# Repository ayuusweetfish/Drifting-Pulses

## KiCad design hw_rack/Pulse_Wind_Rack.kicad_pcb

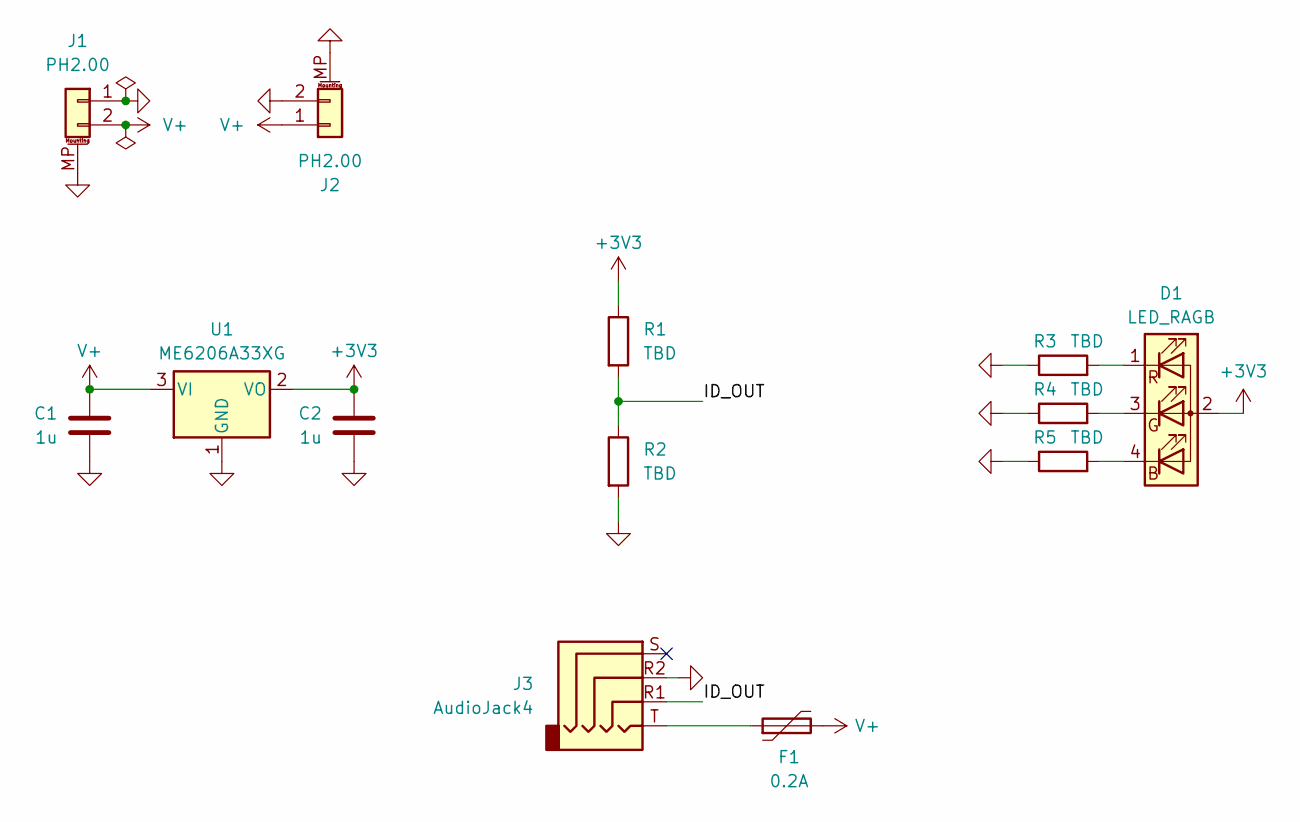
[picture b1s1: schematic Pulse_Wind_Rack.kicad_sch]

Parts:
C1, C2: 1u; C_0402_1005Metric
D1: LED_RAGB; LED_D5.0mm-4_RGB
F1: 0.2A; Fuse_0603_1608Metric
J1, J2: PH2.00; JST_PH_S2B-PH-SM4-TB_1x02-1MP_P2.00mm_Horizontal
J3: AudioJack4; Jack_3.5mm_KoreanHropartsElec_PJ-320D-4A_Horizontal
R1, R2, R3, R4, R5: TBD; R_0402_1005Metric
U1: ME6206A33XG; SOT-23

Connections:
+3V3: C2.2, D1.2 (A), R1.1, U1.2 (VO)
/ID_OUT: J3.R1, R1.2, R2.1
GND: C1.1, C2.1, J1.1, J1.MP (MountPin), J2.2, J2.MP (MountPin), J3.R2, R2.2, R3.1, R4.1, R5.1, U1.1 (GND)
unnamed: D1.4 (BK), R5.2
unnamed: D1.3 (GK), R4.2
unnamed: D1.1 (RK), R3.2
unnamed: F1.1, J3.T
V+: C1.2, F1.2, J1.2, J2.1, U1.3 (VI)

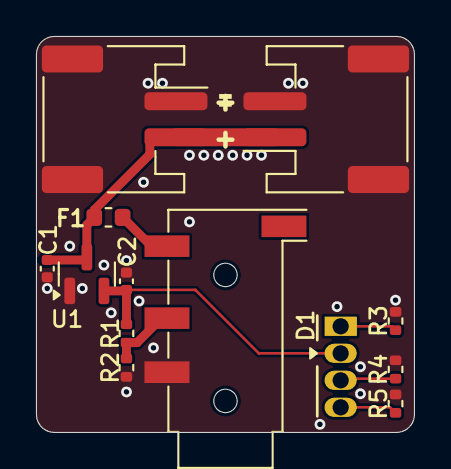
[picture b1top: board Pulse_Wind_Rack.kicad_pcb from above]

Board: 2 copper layers, 21.0 x 22.0 mm, 13 parts (0 on the bottom side), 8 nets.

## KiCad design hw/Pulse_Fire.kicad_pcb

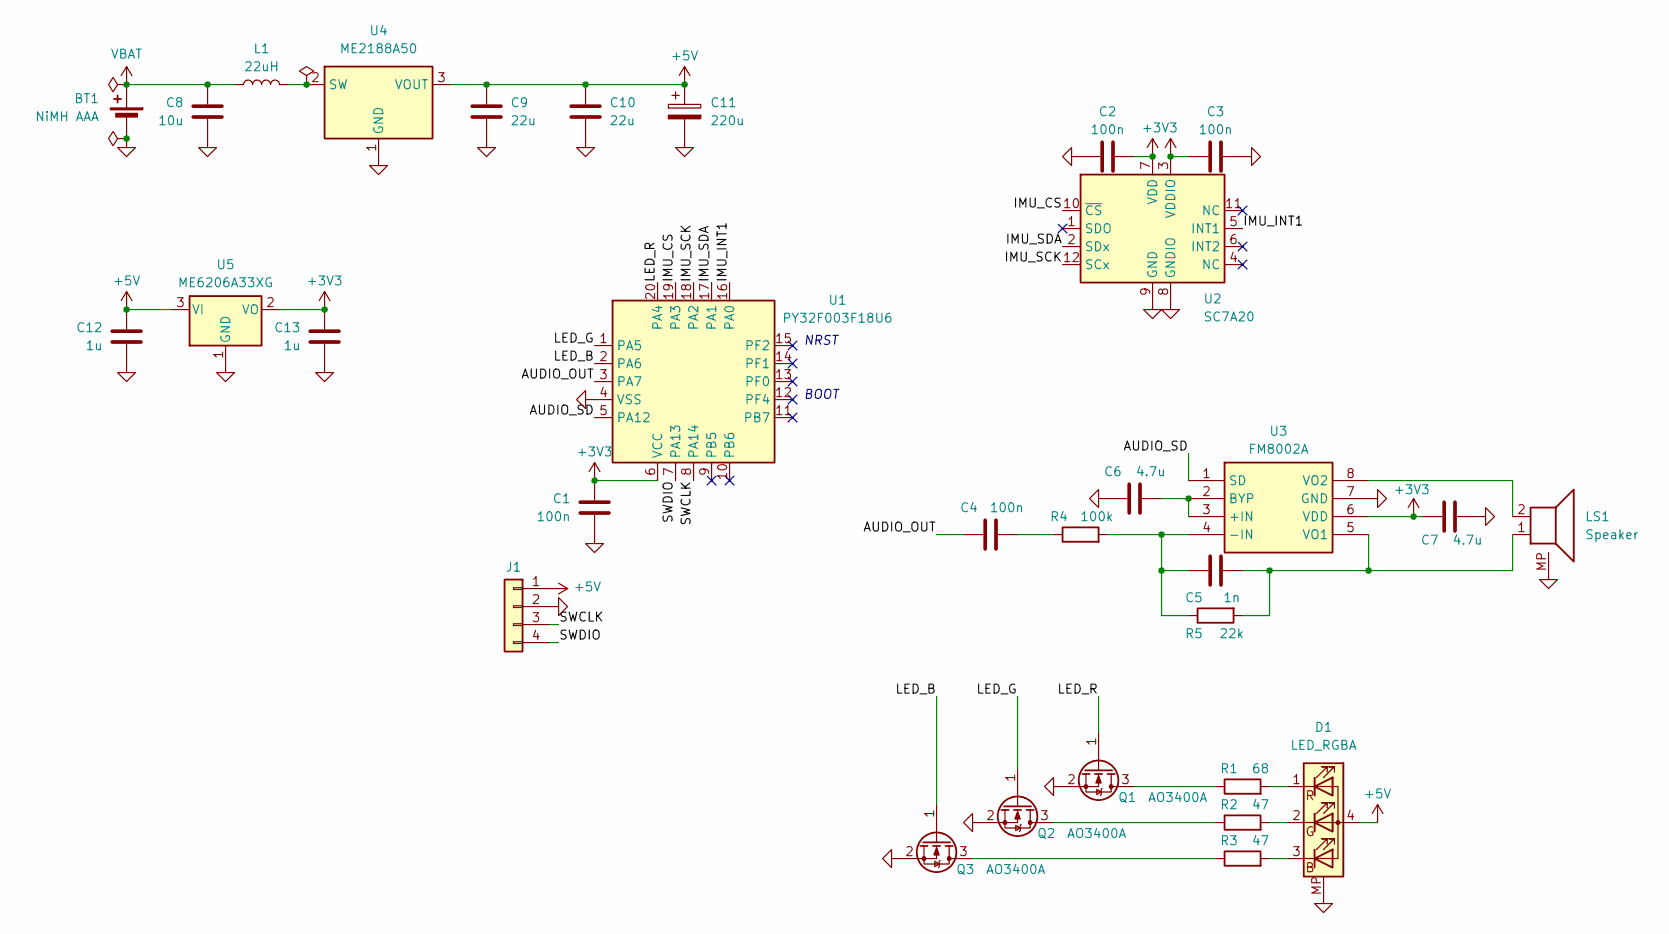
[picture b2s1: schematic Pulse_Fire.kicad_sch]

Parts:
BT1: NiMH AAA; BatteryHolder_Keystone_2466_1xAAA
C1, C2, C3, C4: 100n; C_0402_1005Metric
C5: 1n; C_0402_1005Metric
C6, C7: 4.7u; C_0402_1005Metric
C8: 10u; C_0402_1005Metric
C9, C10: 22u; C_0603_1608Metric
C11: 220u; CP_Elec_6.3x5.4
C12, C13: 1u; C_0402_1005Metric
D1: LED_RGBA; JST_PH_S4B-PH-SM4-TB_1x04-1MP_P2.00mm_Horizontal
J1: Conn_01x04; TestPoints_1x04_P2.00
L1: 22uH; L_Sunlord_SWPA4030S
LS1: Speaker; JST_PH_S2B-PH-SM4-TB_1x02-1MP_P2.00mm_Horizontal
Q1, Q2, Q3: AO3400A; SOT-23
R1: 68; R_0603_1608Metric
R2, R3: 47; R_0603_1608Metric
R4: 100k; R_0402_1005Metric
R5: 22k; R_0402_1005Metric
U1: PY32F003F18U6; QFN-20-1EP_3x3mm_P0.4mm_EP1.65x1.65mm
U2: SC7A20; LGA-12_2x2mm_P0.5mm
U3: FM8002A; SOP-8_3.9x4.9mm_P1.27mm; Manufacturer_Part_Number MD8002A
U4: ME2188A50; SOT-23
U5: ME6206A33XG; SOT-23

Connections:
+3V3: C1.2, C2.2, C3.1, C7.1, C13.2, U1.6 (VCC), U2.3 (VDDIO), U2.7 (VDD), U3.6 (VDD), U5.2 (VO)
+5V: C9.2, C10.2, C11.1, C12.2, D1.4 (A), J1.1, U4.3 (VOUT), U5.3 (VI)
/AUDIO_OUT: C4.1, U1.3 (PA7)
/AUDIO_SD: U1.5 (PA12), U3.1 (SD)
/IMU_CS: U1.19 (PA3), U2.10 (~CS)
/IMU_INT1: U1.16 (PA0), U2.5 (INT1)
/IMU_SCK: U1.18 (PA2), U2.12 (SCx)
/IMU_SDA: U1.17 (PA1), U2.2 (SDx)
/LED_B: Q3.1 (G), U1.2 (PA6)
/LED_G: Q2.1 (G), U1.1 (PA5)
/LED_R: Q1.1 (G), U1.20 (PA4)
/SWCLK: J1.3, U1.8 (PA14)
/SWDIO: J1.4, U1.7 (PA13)
GND: BT1.2 (-), C1.1, C2.1, C3.2, C6.1, C7.2, C8.1, C9.1, C10.1, C11.2, C12.1, C13.1, D1.MP, J1.2, LS1.MP, Q1.2 (S), Q2.2 (S), Q3.2 (S), U1.4 (VSS), U1.21 (PAD), U2.8 (GNDIO), U2.9 (GND), U3.7 (GND), U4.1 (GND), U5.1 (GND)
unnamed: C4.2, R4.1
unnamed: D1.3 (BK), R3.2
unnamed: D1.2 (GK), R2.2
unnamed: D1.1 (RK), R1.2
unnamed: Q1.3 (D), R1.1
unnamed: Q2.3 (D), R2.1
unnamed: Q3.3 (D), R3.1
unnamed: C6.2, U3.2 (BYP), U3.3 (+IN)
unnamed: C5.1, R4.2, R5.1, U3.4 (-IN)
unnamed: C5.2, LS1.1, R5.2, U3.5 (VO1)
unnamed: LS1.2, U3.8 (VO2)
unnamed: L1.2, U4.2 (SW)
VBAT: BT1.1 (+), C8.2, L1.1

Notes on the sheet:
NRST
BOOT

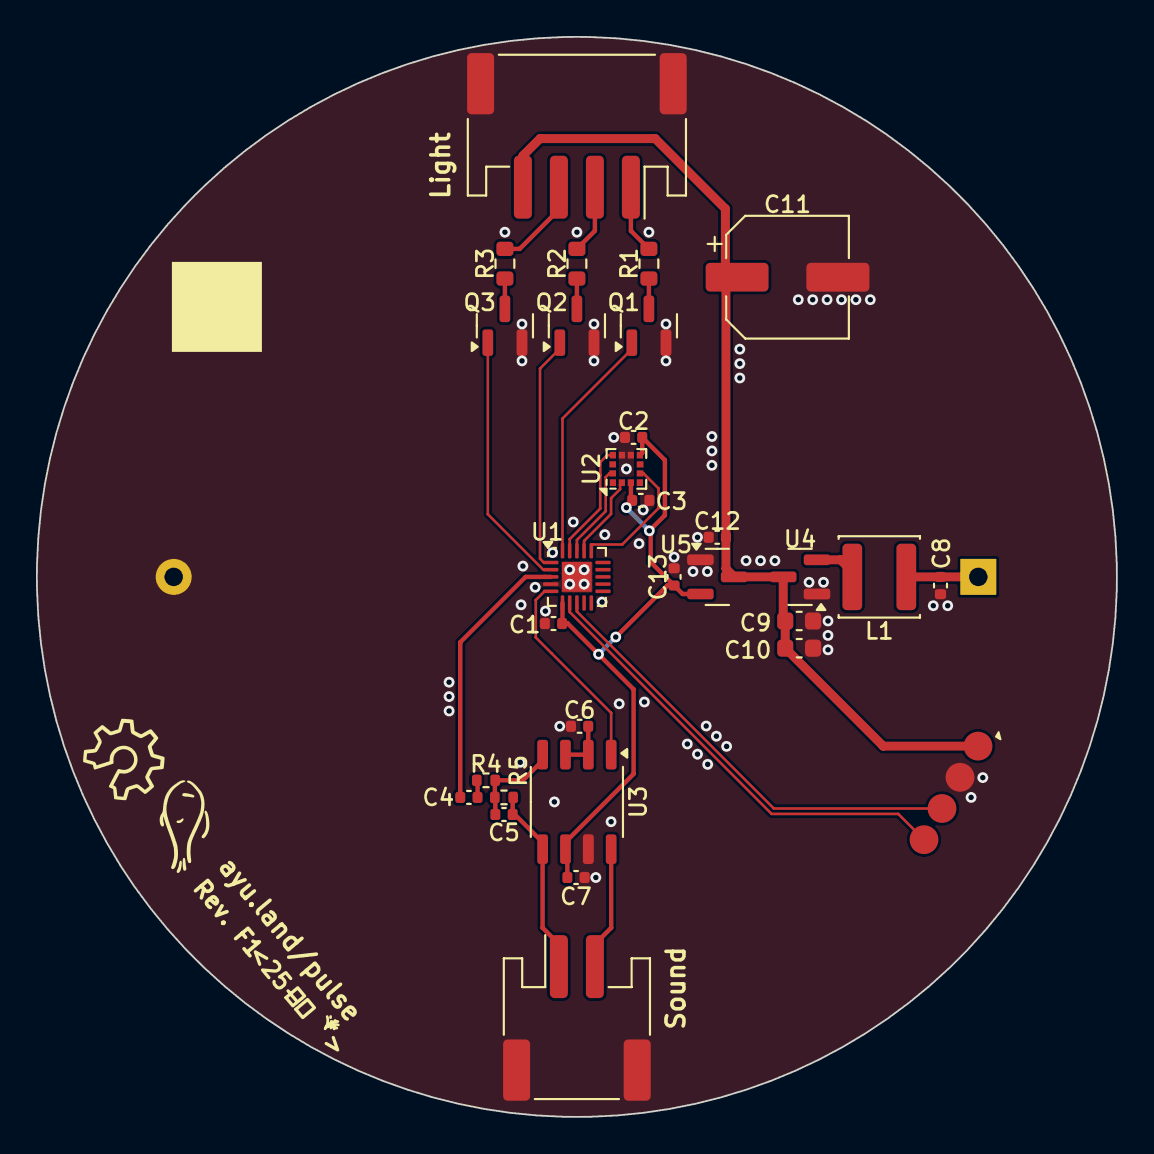
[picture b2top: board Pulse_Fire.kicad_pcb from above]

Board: 2 copper layers, 60.0 x 60.0 mm, 31 parts (1 on the bottom side), 27 nets.

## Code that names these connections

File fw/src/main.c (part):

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  HAL_GPIO_Init(GPIOA, &(GPIO_InitTypeDef){
    .Mode = GPIO_MODE_AF_PP,
    .Pin = (1 << 4) | (1 << 5),
    .Alternate = 13,  // PA4 = TIM3_CH3, PA5 = TIM3_CH2
    .Speed = GPIO_SPEED_FREQ_HIGH,
  });
  HAL_GPIO_Init(GPIOA, &(GPIO_InitTypeDef){
    .Mode = GPIO_MODE_AF_PP,
    .Pin = (1 << 6),
    .Alternate = 1,   // PA6 = TIM3_CH1
    .Speed = GPIO_SPEED_FREQ_HIGH,
  });

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
  // ============ Audio output ============ //
{
  // PA12 = AUDIO_SD
  GPIOA->BSRR = (1 << 12);  // High = disable
  HAL_GPIO_Init(GPIOA, &(GPIO_InitTypeDef){
    .Mode = GPIO_MODE_OUTPUT_PP,
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  HAL_GPIO_Init(GPIOA, &(GPIO_InitTypeDef){
    .Mode = GPIO_MODE_AF_PP,
    .Pin = (1 << 7),
    .Alternate = 5,   // PA7 = TIM17_CH1
    .Speed = GPIO_SPEED_FREQ_HIGH,
  });
  HAL_TIM_PWM_Init(&tim17);
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    },
  };
  HAL_SPI_Init(&spi1);
  GPIOA->BSRR = (1 << 3);   // IMU_CS high
  HAL_GPIO_Init(GPIOA, &(GPIO_InitTypeDef){
    .Mode = GPIO_MODE_OUTPUT_PP,
    .Pin = (1 << 3),
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  HAL_GPIO_Init(GPIOA, &(GPIO_InitTypeDef){
    .Mode = GPIO_MODE_AF_PP,
    .Pin = (1 << 1) | (1 << 2),
    .Alternate = 10,  // PA1 = SPI1_MOSI, PA2 = SPI1_SCK
  });
}

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  printf("IMU FIFO cleared\n");

if (0)
  GPIOA->BSRR = (1 << 12) << 16;  // Enable by AUDIO_SD

  while (1) {
    bool pat = false;
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
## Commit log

2025-08-05 hw: Bob-part schematic
2025-08-05 hw: Layout & routing
2025-08-05 hw: Tweaks in the details
2025-08-05 hw: Adjust silkscreen
2025-08-05 hw: Finalize board design
2025-08-06 hw: Fix errors (> <)
2025-08-06 hw: Connect SC7A20 NC (pin 4) to GND?
2025-08-06 hw: Minor tweaks; finalize
2025-08-06 hw: Rack schematic
2025-08-06 fw: Rack board? To be revised
2025-08-06 fw: Revise rack board layout & routing
2025-08-06 hw: Finalize rack board design
2025-08-07 hw: Schematic
2025-08-07 hw: Revise schematic to use discrete MOSFETs
2025-08-08 hw: Schematic -- add mounting pins for JST connectors
2025-08-08 hw: Complete board design
2025-08-08 hw: Detail nudges
2025-08-08 hw: Place silkscreen
2025-08-08 hw: Embed fonts; revise silkscreen
2025-08-08 hw: Output Gerbers
2025-08-09 mech: Add rack 3D model
2025-08-09 mech: Save block material
2025-08-09 mech: Split shell's front side into separate part
2025-08-09 mech: Adjust parameters; test print
2025-08-10 mech: Holders (WIP)
2025-08-11 fw: Initial framework (based on Meteorites-Bianqing)
2025-08-11 fw: Re-organize debugging helpers
2025-08-11 fw: Read WHO_AM_I register from IMU
    WHO_AM_I = 0x34?
2025-08-11 fw: Correctly reading WHO_AM_I
2025-08-11 fw: Set up FIFO (Non-working)
2025-08-11 fw: Correctly read from IMU's FIFO
2025-08-11 fw: Fade LED
2025-08-11 fw: Run audio PWM with DMA
2025-08-11 fw: Correct clock frequency (8 MHz -> 24 MHz)
2025-08-12 fw: Output sound waves
2025-08-12 fw: Read ADC
    Reading VCC/2 results in 1950~1960
2025-08-13 hw: Add polyfuse in rack board
2025-08-17 fw: Blink LED with pendulum
    Not apparent enough
2025-08-17 fw: Use the acceleration along the radial axis?
2025-08-17 fw: Tone onset and envelope
2025-08-17 fw: Reduce volume
2025-08-17 hw: Comment schematic with actual components used
2025-08-18 fw: Copy firmware from Wind (908d7a5)
2025-08-18 fw: Disable ADC; enable EXTI
2025-08-18 fw: Invert PWM polarity to match NMOS driver
2025-08-18 fw: Combined tests of light, speaker, and IMU
2025-08-18 fw: Simultaneous sound & light testrun
2025-08-21 fw: Reorganize; move all general-use files to `base/`
2025-08-21 fw: Silence irrelevant linker warnings
    Unused I/O-related syscalls: `_read`, `_write`, etc. are "not implemented and will always fail"
2025-08-21 fw: Clean-up
2025-08-21 fw: Work again with debug; improve debugging DX
2025-08-21 fw: Working pat detection
2025-08-21 fw: Switch from `nosys` to `nano` specs
2025-08-22 fw: Drive amplifier enable/shutdown pin
2025-08-22 fw: Current draw test
2026-01-12 fw: Update Makefile
    Based on Slodycz:7b86dd8
2026-01-18 fw: Fix light cannot be fully off
2026-01-18 fw: Reset before erasing
2026-01-18 fw: Cycling pitch(?)es
2026-01-18 fw: Clear IMU FIFO on boot to prevent excessive glitch
2026-01-18 fw: Increase light intensity
2026-01-23 fw: Enable audio again, and disable again
    Speaker seems to interfere with IMU power supply (?) so disabled again
2026-01-23 fw: More colours ✨🌈
2026-01-24 mech: Make room for wires
2026-01-24 mech: A new holder
2026-01-25 fw: Add white light test
2026-01-25 fw: Increase intensity to full range
2026-01-25 mech: Revise base model
2026-02-01 fw: Upgrade firmware library 1.4.7 -> 1.5.0
